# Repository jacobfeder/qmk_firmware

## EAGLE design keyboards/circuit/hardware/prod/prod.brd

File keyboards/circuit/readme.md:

cd to qmk_firmware directory.

Install dependencies using script in util/install_dependencies.sh

```shell
$ sudo util/<your os>_install.sh
```

To program, start keyboard in bootloader mode using BOOTMAGIC by holding down SPACE+B during boot (2-3 sec) then run the following command from the qmk_firmware top level directory (use an on-screen keyboard to press enter key for you to run this command):

```shell
$ make circuit:default:dfu
```

Make your own custom layout by duplicating the "default" folder in keyboards/circuit and modifying as necessary. Flash it to your keyboard by running:

```shell
$ make circuit:<your layout name>:dfu
```

Troubleshooting:

By default Make uses `sh` instead of `bash` for its shell commands. If you are running into strange errors, try using bash instead by calling Make like so:

```shell
$ make circuit:default SHELL=/bin/bash
```

Also, if you get an error that says "bootloader not found" or "device not found", try running the above Make command with ``sudo``.

To program using ICSP run `avrdude_prog_icsp.sh ../../circuit_default_production.hex` in 'keyboards/circuit' directory with arduino as ICSP.

Raw data (keyboard-layout-editor.com):

[{c:"#f67f00",t:"#1a1a1a",a:7},"esc",{c:"#d0ccc0",t:"#000000",a:5},"!\n1","@\n2","#\n3","$\n4","%\n5","^\n6","&\n7","*\n8","(\n9",{a:4,fa:[0,0,0,1]},")\n0\n\n/F10",{c:"#96938e"},"_\n-\n\n/F11","+\n=\n\n/F12",{a:5},"|\n\\","~\n`"],
[{c:"#60605b",t:"#d0ccc0",a:7,w:1.5},"tab",{c:"#d0ccc0",t:"#000000"},"Q","W","E","R","T","Y","U","I","O","P",{c:"#96938e",a:5},"{\n[","}\n]",{c:"#5eb1e7",t:"#1a1a1a",a:4,w:1.5},"\n\n\n/delete\n\n\n\n\n\n<i class='kb kb-Unicode-BackSpace-DeleteLeft-Big'></i>"],
[{c:"#60605b",t:"#d0ccc0",w:1.75},"\n\n\n/caps\n\n\n\n\n\nterminal",{c:"#d0ccc0",t:"#000000",a:7},"A","S","D",{n:true},"F","G","H",{n:true},"J","K","L",{c:"#96938e",a:5},":\n;","\"\n'",{c:"#60605b",t:"#d0ccc0",a:7,w:2.25},"sudo rm -rf /"],
[{w:2.25},"shift",{c:"#d0ccc0",t:"#000000"},"Z","X","C","V","B","N","M",{c:"#96938e",a:5},"<\n,",">\n.","?\n/",{c:"#60605b",t:"#d0ccc0",a:7,w:2.75},"shift"],
[{w:1.5},"ctrl","<i class='fa fa-television'></i>",{w:1.5},"alt",{c:"#d0ccc0",t:"#000000",w:6},"",{c:"#60605b",t:"#d0ccc0"},"fn",{c:"#f67f00",t:"#000000",a:4},"\n\n\n/home\n\n\n\n\n\n<i class='fa fa-chevron-left'></i>","\n\n\n/pgup\n\n\n\n\n\n<i class='fa fa-chevron-up'></i>","\n\n\n/pgdn\n\n\n\n\n\n<i class='fa fa-chevron-down'></i>","\n\n\n/end\n\n\n\n\n\n<i class='fa fa-chevron-right'></i>"]

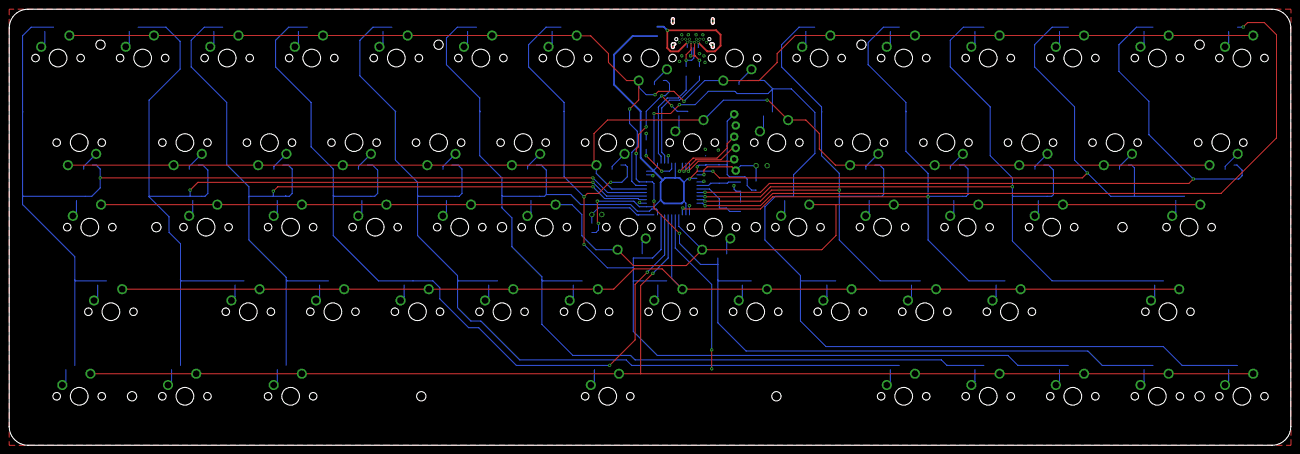
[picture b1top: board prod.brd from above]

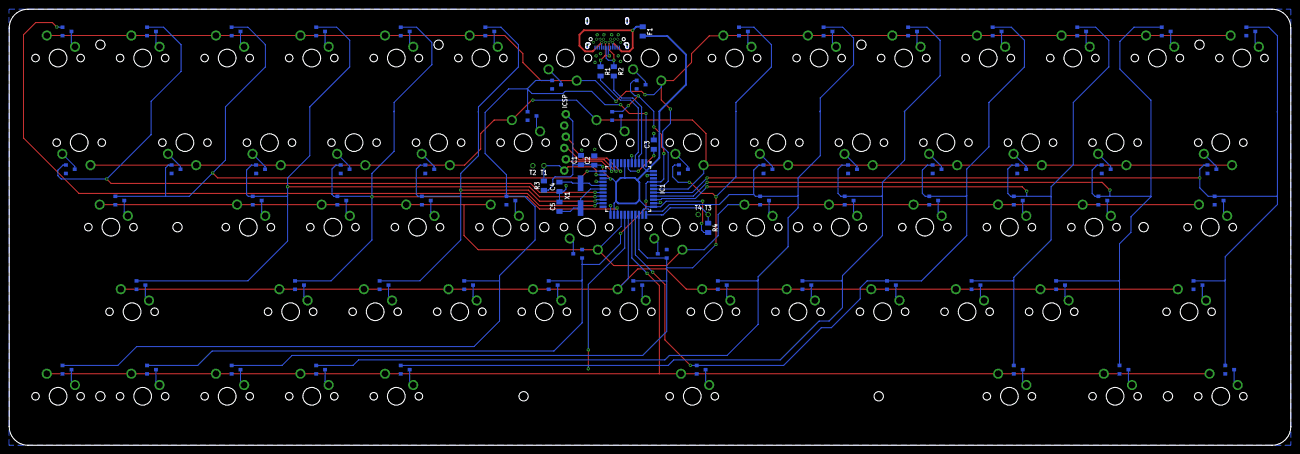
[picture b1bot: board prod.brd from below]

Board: 2 copper layers, 288.7 x 98.2 mm, 144 parts (81 on the bottom side), 98 nets.

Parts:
C1, C3: 1u; 0805
C2: 100n; 0805
C4, C5: 18p; 0805
D_0, D_1, D_2, D_3, D_4, D_5, D_6, D_7, D_8, D_9: DIODE-BAS16L; SOT23-3
D_A: DIODE-BAS16L; SOT23-3
D_B: DIODE-BAS16L; SOT23-3
D_BCK: DIODE-BAS16L; SOT23-3
D_C: DIODE-BAS16L; SOT23-3
D_CAPS: DIODE-BAS16L; SOT23-3
D_COLON: DIODE-BAS16L; SOT23-3
D_D: DIODE-BAS16L; SOT23-3
D_DA: DIODE-BAS16L; SOT23-3
D_E: DIODE-BAS16L; SOT23-3
D_ENTER: DIODE-BAS16L; SOT23-3
D_ESC: DIODE-BAS16L; SOT23-3
D_F: DIODE-BAS16L; SOT23-3
D_FN: DIODE-BAS16L; SOT23-3
D_G: DIODE-BAS16L; SOT23-3
D_GT: DIODE-BAS16L; SOT23-3
D_H: DIODE-BAS16L; SOT23-3
D_I: DIODE-BAS16L; SOT23-3
D_J: DIODE-BAS16L; SOT23-3
D_K: DIODE-BAS16L; SOT23-3
D_L: DIODE-BAS16L; SOT23-3
D_LA: DIODE-BAS16L; SOT23-3
D_LALT: DIODE-BAS16L; SOT23-3
D_LCTRL: DIODE-BAS16L; SOT23-3
D_LCURL: DIODE-BAS16L; SOT23-3
D_LSHIFT: DIODE-BAS16L; SOT23-3
D_LT: DIODE-BAS16L; SOT23-3
D_M: DIODE-BAS16L; SOT23-3
D_MINUS: DIODE-BAS16L; SOT23-3
D_N: DIODE-BAS16L; SOT23-3
D_O: DIODE-BAS16L; SOT23-3
D_OS: DIODE-BAS16L; SOT23-3
D_P: DIODE-BAS16L; SOT23-3
D_PIPE: DIODE-BAS16L; SOT23-3
D_PLUS: DIODE-BAS16L; SOT23-3
D_Q: DIODE-BAS16L; SOT23-3
D_QM: DIODE-BAS16L; SOT23-3
D_QUOTE: DIODE-BAS16L; SOT23-3
D_R: DIODE-BAS16L; SOT23-3
D_RA: DIODE-BAS16L; SOT23-3
D_RCURL: DIODE-BAS16L; SOT23-3
D_RSHIFT: DIODE-BAS16L; SOT23-3
D_S: DIODE-BAS16L; SOT23-3
D_SPACE: DIODE-BAS16L; SOT23-3
D_T: DIODE-BAS16L; SOT23-3
D_TAB: DIODE-BAS16L; SOT23-3
D_TILDE: DIODE-BAS16L; SOT23-3
D_U: DIODE-BAS16L; SOT23-3
D_UA: DIODE-BAS16L; SOT23-3
D_V: DIODE-BAS16L; SOT23-3
D_W: DIODE-BAS16L; SOT23-3
D_X: DIODE-BAS16L; SOT23-3
D_Y: DIODE-BAS16L; SOT23-3
D_Z: DIODE-BAS16L; SOT23-3
F1: 500m; 0805
IC1: ATMEGA32U4; QFP80P1200X1225X120-44
ICSP: HEADER-061X6; HEADER-06
J1: USB-C-2.0-CUI-UJ31-CH-G1-SMT-TR; USB-C-CUI-UJ31-CH-G1-SMT-TR
R1, R2: 22; 0805
R3, R4: 10k; 0805
SW_0, SW_1, SW_2, SW_3, SW_4, SW_5, SW_6, SW_7, SW_8, SW_9: SWITCH-SPSTCHERRY; CHERRY-MX
SW_A: SWITCH-SPSTCHERRY; CHERRY-MX
SW_B: SWITCH-SPSTCHERRY; CHERRY-MX
SW_BCK: SWITCH-SPSTCHERRY; CHERRY-MX
SW_C: SWITCH-SPSTCHERRY; CHERRY-MX
SW_CAPS: SWITCH-SPSTCHERRY; CHERRY-MX
SW_COLON: SWITCH-SPSTCHERRY; CHERRY-MX
SW_D: SWITCH-SPSTCHERRY; CHERRY-MX
SW_DA: SWITCH-SPSTCHERRY; CHERRY-MX
SW_E: SWITCH-SPSTCHERRY; CHERRY-MX
SW_ENTER: SWITCH-SPSTCHERRY; CHERRY-MX
SW_ESC: SWITCH-SPSTCHERRY; CHERRY-MX
SW_F: SWITCH-SPSTCHERRY; CHERRY-MX
SW_FN: SWITCH-SPSTCHERRY; CHERRY-MX
SW_G: SWITCH-SPSTCHERRY; CHERRY-MX
SW_GT: SWITCH-SPSTCHERRY; CHERRY-MX
SW_H: SWITCH-SPSTCHERRY; CHERRY-MX
SW_I: SWITCH-SPSTCHERRY; CHERRY-MX
SW_J: SWITCH-SPSTCHERRY; CHERRY-MX
SW_K: SWITCH-SPSTCHERRY; CHERRY-MX
SW_LA: SWITCH-SPSTCHERRY; CHERRY-MX
SW_LALT: SWITCH-SPSTCHERRY; CHERRY-MX
SW_LCTRL: SWITCH-SPSTCHERRY; CHERRY-MX
SW_LCURL: SWITCH-SPSTCHERRY; CHERRY-MX
SW_LSHIFT: SWITCH-SPSTCHERRY; CHERRY-MX
SW_LT: SWITCH-SPSTCHERRY; CHERRY-MX
SW_M: SWITCH-SPSTCHERRY; CHERRY-MX
SW_MINUS: SWITCH-SPSTCHERRY; CHERRY-MX
SW_N: SWITCH-SPSTCHERRY; CHERRY-MX
SW_O: SWITCH-SPSTCHERRY; CHERRY-MX
SW_OS: SWITCH-SPSTCHERRY; CHERRY-MX
SW_P: SWITCH-SPSTCHERRY; CHERRY-MX
SW_PIPE: SWITCH-SPSTCHERRY; CHERRY-MX
SW_PLUS: SWITCH-SPSTCHERRY; CHERRY-MX
SW_Q: SWITCH-SPSTCHERRY; CHERRY-MX
SW_QM: SWITCH-SPSTCHERRY; CHERRY-MX
SW_QUOTE: SWITCH-SPSTCHERRY; CHERRY-MX
SW_R: SWITCH-SPSTCHERRY; CHERRY-MX
SW_RA: SWITCH-SPSTCHERRY; CHERRY-MX
SW_RCURL: SWITCH-SPSTCHERRY; CHERRY-MX
SW_RSHIFT: SWITCH-SPSTCHERRY; CHERRY-MX
SW_S: SWITCH-SPSTCHERRY; CHERRY-MX
SW_SPACE: SWITCH-SPSTCHERRY; CHERRY-MX
SW_T: SWITCH-SPSTCHERRY; CHERRY-MX
SW_TAB: SWITCH-SPSTCHERRY; CHERRY-MX
SW_TILDE: SWITCH-SPSTCHERRY; CHERRY-MX
SW_U: SWITCH-SPSTCHERRY; CHERRY-MX
SW_UA: SWITCH-SPSTCHERRY; CHERRY-MX
SW_V: SWITCH-SPSTCHERRY; CHERRY-MX
SW_W: SWITCH-SPSTCHERRY; CHERRY-MX
SW_X: SWITCH-SPSTCHERRY; CHERRY-MX
SW_Y: SWITCH-SPSTCHERRY; CHERRY-MX
SW_Z: SWITCH-SPSTCHERRY; CHERRY-MX
S_L: SWITCH-SPSTCHERRY; CHERRY-MX
T1, T2, T3, T4: TEST-POINT
X1: 16MHz; CRYSTAL-SMD

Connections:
COL1: D_CAPS.1, D_ESC.1, D_LCTRL.1, D_LSHIFT.1, D_TAB.1, IC1.38
COL2: D_1.1, D_A.1, D_OS.1, D_Q.1, D_Z.1, IC1.37
COL3: D_2.1, D_LALT.1, D_S.1, D_W.1, D_X.1, IC1.36
COL4: D_3.1, D_C.1, D_D.1, D_E.1, D_SPACE.1, IC1.30
COL5: D_4.1, D_F.1, D_FN.1, D_R.1, D_V.1, IC1.27
COL6: D_5.1, D_B.1, D_G.1, D_LA.1, D_T.1, IC1.32
COL7: D_6.1, D_H.1, D_N.1, D_UA.1, D_Y.1, IC1.31
COL8: D_7.1, D_DA.1, D_J.1, D_M.1, D_U.1, IC1.41
COL9: D_8.1, D_I.1, D_K.1, D_LT.1, D_RA.1, IC1.1
COL10: D_9.1, D_GT.1, D_L.1, D_O.1, IC1.20
COL11: D_0.1, D_COLON.1, D_P.1, D_QM.1, IC1.25
COL12: D_LCURL.1, D_MINUS.1, D_QUOTE.1, D_RSHIFT.1, IC1.19
COL13: D_ENTER.1, D_PLUS.1, D_RCURL.1, IC1.12
COL14: D_BCK.1, D_PIPE.1, IC1.18
COL15: D_TILDE.1, IC1.21
GND: C1.2, C2.2, C3.2, C4.2, C5.1, IC1.5, IC1.15, IC1.23, IC1.35, IC1.43, ICSP.2, J1.GND@1, J1.GND@2, J1.GND@3, J1.GND@4, J1.GND@5, J1.GND@6, J1.GND@7, J1.GND@8, T2.P$1, T4.P$1
unnamed: J1.D+@1, J1.D+@2, R1.1
unnamed: J1.D-@1, J1.D-@2, R2.1
unnamed: IC1.4, R1.2
unnamed: C4.1, IC1.16, X1.P$2
unnamed: F1.1, J1.VBUS@1, J1.VBUS@2, J1.VBUS@3, J1.VBUS@4
unnamed: IC1.3, R2.2
unnamed: IC1.11, ICSP.5
unnamed: C3.1, IC1.6
unnamed: C5.2, IC1.17, X1.P$1
unnamed: D_ESC.3, SW_ESC.P$1
unnamed: IC1.10, ICSP.4
unnamed: IC1.9, ICSP.3
unnamed: IC1.33, R4.2, T3.P$1
unnamed: D_TAB.3, SW_TAB.P$1
unnamed: D_CAPS.3, SW_CAPS.P$1
unnamed: D_LSHIFT.3, SW_LSHIFT.P$1
unnamed: D_LCTRL.3, SW_LCTRL.P$1
unnamed: D_1.3, SW_1.P$1
unnamed: D_Q.3, SW_Q.P$1
unnamed: D_A.3, SW_A.P$1
unnamed: D_Z.3, SW_Z.P$1
unnamed: D_OS.3, SW_OS.P$1
unnamed: D_2.3, SW_2.P$1
unnamed: D_W.3, SW_W.P$1
unnamed: D_S.3, SW_S.P$1
unnamed: D_X.3, SW_X.P$1
unnamed: D_LALT.3, SW_LALT.P$1
unnamed: D_3.3, SW_3.P$1
unnamed: D_E.3, SW_E.P$1
unnamed: D_D.3, SW_D.P$1
unnamed: D_C.3, SW_C.P$1
unnamed: D_SPACE.3, SW_SPACE.P$1
unnamed: D_4.3, SW_4.P$1
unnamed: D_R.3, SW_R.P$1
unnamed: D_F.3, SW_F.P$1
unnamed: D_V.3, SW_V.P$1
unnamed: D_FN.3, SW_FN.P$1
unnamed: D_5.3, SW_5.P$1
unnamed: D_T.3, SW_T.P$1
unnamed: D_G.3, SW_G.P$1
unnamed: D_B.3, SW_B.P$1
unnamed: D_LA.3, SW_LA.P$1
unnamed: D_6.3, SW_6.P$1
unnamed: D_Y.3, SW_Y.P$1
unnamed: D_H.3, SW_H.P$1
unnamed: D_N.3, SW_N.P$1
unnamed: D_UA.3, SW_UA.P$1
unnamed: D_7.3, SW_7.P$1
unnamed: D_U.3, SW_U.P$1
unnamed: D_J.3, SW_J.P$1
unnamed: D_M.3, SW_M.P$1
unnamed: D_DA.3, SW_DA.P$1
unnamed: D_8.3, SW_8.P$1
unnamed: D_I.3, SW_I.P$1
unnamed: D_K.3, SW_K.P$1
unnamed: D_LT.3, SW_LT.P$1
unnamed: D_RA.3, SW_RA.P$1
unnamed: D_9.3, SW_9.P$1
unnamed: D_O.3, SW_O.P$1
unnamed: D_L.3, S_L.P$1
unnamed: D_GT.3, SW_GT.P$1
unnamed: D_0.3, SW_0.P$1
unnamed: D_P.3, SW_P.P$1
unnamed: D_COLON.3, SW_COLON.P$1
unnamed: D_QM.3, SW_QM.P$1
unnamed: D_MINUS.3, SW_MINUS.P$1
unnamed: D_LCURL.3, SW_LCURL.P$1
unnamed: D_QUOTE.3, SW_QUOTE.P$1
unnamed: D_RSHIFT.3, SW_RSHIFT.P$1
unnamed: D_PLUS.3, SW_PLUS.P$1
unnamed: D_RCURL.3, SW_RCURL.P$1
unnamed: D_ENTER.3, SW_ENTER.P$1
unnamed: D_PIPE.3, SW_PIPE.P$1
unnamed: D_BCK.3, SW_BCK.P$1
unnamed: D_TILDE.3, SW_TILDE.P$1
RESET: IC1.13, ICSP.6, R3.1, T1.P$1
ROW1: IC1.40, SW_0.P$2, SW_1.P$2, SW_2.P$2, SW_3.P$2, SW_4.P$2, SW_5.P$2, SW_6.P$2, SW_7.P$2, SW_8.P$2, SW_9.P$2, SW_ESC.P$2, SW_MINUS.P$2, SW_PIPE.P$2, SW_PLUS.P$2, SW_TILDE.P$2
ROW2: IC1.39, SW_BCK.P$2, SW_E.P$2, SW_I.P$2, SW_LCURL.P$2, SW_O.P$2, SW_P.P$2, SW_Q.P$2, SW_R.P$2, SW_RCURL.P$2, SW_T.P$2, SW_TAB.P$2, SW_U.P$2, SW_W.P$2, SW_Y.P$2
ROW3: IC1.26, SW_A.P$2, SW_CAPS.P$2, SW_COLON.P$2, SW_D.P$2, SW_ENTER.P$2, SW_F.P$2, SW_G.P$2, SW_H.P$2, SW_J.P$2, SW_K.P$2, SW_QUOTE.P$2, SW_S.P$2, S_L.P$2
ROW4: IC1.28, SW_B.P$2, SW_C.P$2, SW_GT.P$2, SW_LSHIFT.P$2, SW_LT.P$2, SW_M.P$2, SW_N.P$2, SW_QM.P$2, SW_RSHIFT.P$2, SW_V.P$2, SW_X.P$2, SW_Z.P$2
ROW5: IC1.29, SW_DA.P$2, SW_FN.P$2, SW_LA.P$2, SW_LALT.P$2, SW_LCTRL.P$2, SW_OS.P$2, SW_RA.P$2, SW_SPACE.P$2, SW_UA.P$2
V+5: C1.1, C2.1, F1.2, IC1.2, IC1.7, IC1.14, IC1.24, IC1.34, IC1.44, ICSP.1, R3.2, R4.1

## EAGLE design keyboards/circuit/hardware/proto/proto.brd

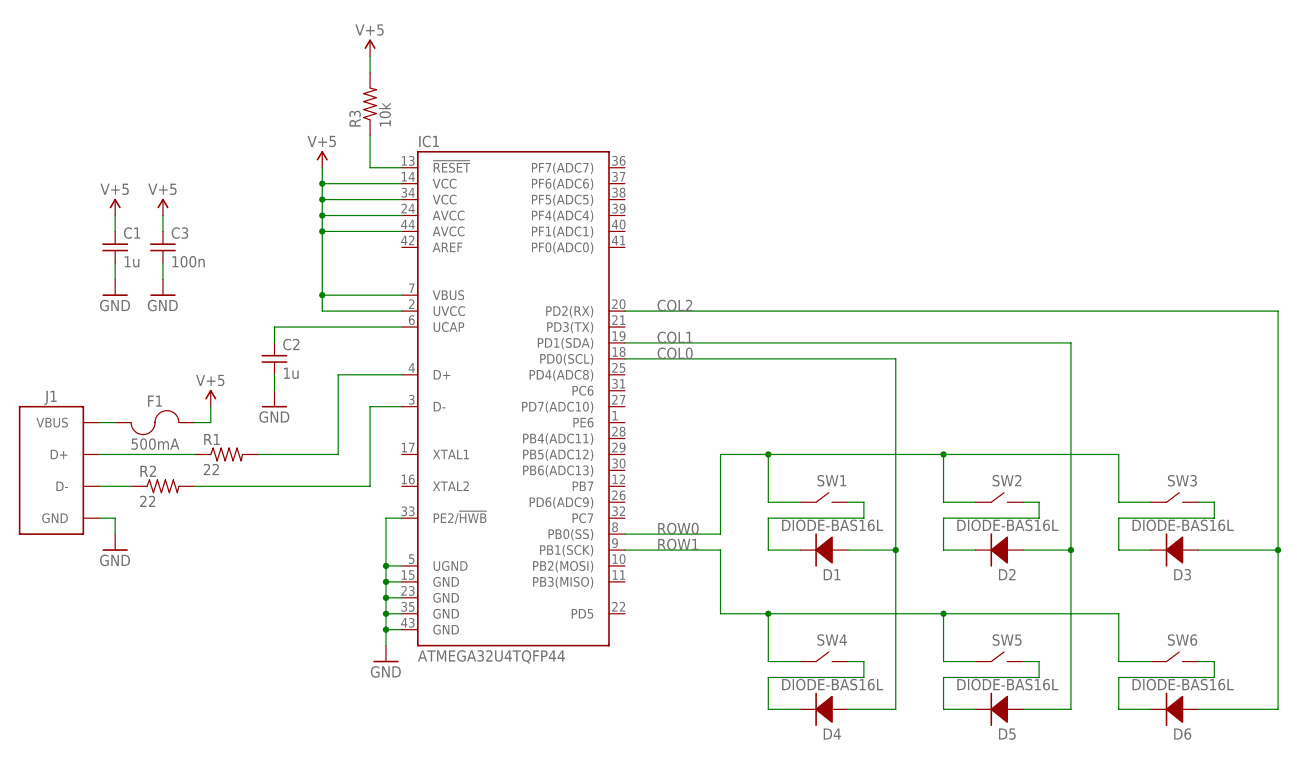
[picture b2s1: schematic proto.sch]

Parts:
C1, C2: 1u; 0805
C3: 100n; 0805
D1, D2, D3, D4, D5, D6: DIODE-BAS16L; SOT23-3
F1: 500mA; 0805
IC1: ATMEGA32U4TQFP44; QFP80P1200X1225X120-44
J1: USB2.0-C; USB-C
R1, R2: 22; 0805
R3: 10k; 0805
SW1, SW2, SW3, SW4, SW5, SW6: SWITCH-SPSTCHERRY; CHERRY-MX

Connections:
COL0: D1.1 (ANODE+), D4.1 (ANODE+), IC1.18 (PD0(SCL))
COL1: D2.1 (ANODE+), D5.1 (ANODE+), IC1.19 (PD1(SDA))
COL2: D3.1 (ANODE+), D6.1 (ANODE+), IC1.20 (PD2(RX))
GND: C1.2, C2.2, C3.2, IC1.5 (UGND), IC1.15 (GND), IC1.23 (GND), IC1.33 (PE2/!HWB), IC1.35 (GND), IC1.43 (GND), J1.GND@1 (GND), J1.GND@2 (GND), J1.GND@3 (GND), J1.GND@4 (GND), J1.GND@5 (GND), J1.GND@6 (GND), J1.GND@7 (GND), J1.GND@8 (GND), J1.GND@9 (GND), J1.GND@10 (GND), J1.GND@11 (GND), J1.GND@12 (GND), J1.GND@13 (GND), J1.GND@14 (GND), J1.GND@15 (GND), J1.GND@16 (GND)
unnamed: J1.D+@1 (D+), J1.D+@2 (D+), R1.1
unnamed: J1.D-@1 (D-), J1.D-@2 (D-), R2.1
unnamed: F1.1, J1.VBUS@1 (VBUS), J1.VBUS@2 (VBUS), J1.VBUS@3 (VBUS), J1.VBUS@4 (VBUS)
unnamed: C2.1, IC1.6 (UCAP)
unnamed: IC1.4 (D+), R1.2
unnamed: IC1.3 (D-), R2.2
unnamed: IC1.13 (!RESET), R3.1
unnamed: D1.3 (CATHODE-), SW1.P$2
unnamed: D2.3 (CATHODE-), SW2.P$2
unnamed: D3.3 (CATHODE-), SW3.P$2
unnamed: D4.3 (CATHODE-), SW4.P$2
unnamed: D5.3 (CATHODE-), SW5.P$2
unnamed: D6.3 (CATHODE-), SW6.P$2
ROW0: IC1.8 (PB0(SS)), SW1.P$1, SW2.P$1, SW3.P$1
ROW1: IC1.9 (PB1(SCK)), SW4.P$1, SW5.P$1, SW6.P$1
V+5: C1.1, C3.1, F1.2, IC1.2 (UVCC), IC1.7 (VBUS), IC1.14 (VCC), IC1.24 (AVCC), IC1.34 (VCC), IC1.44 (AVCC), R3.2

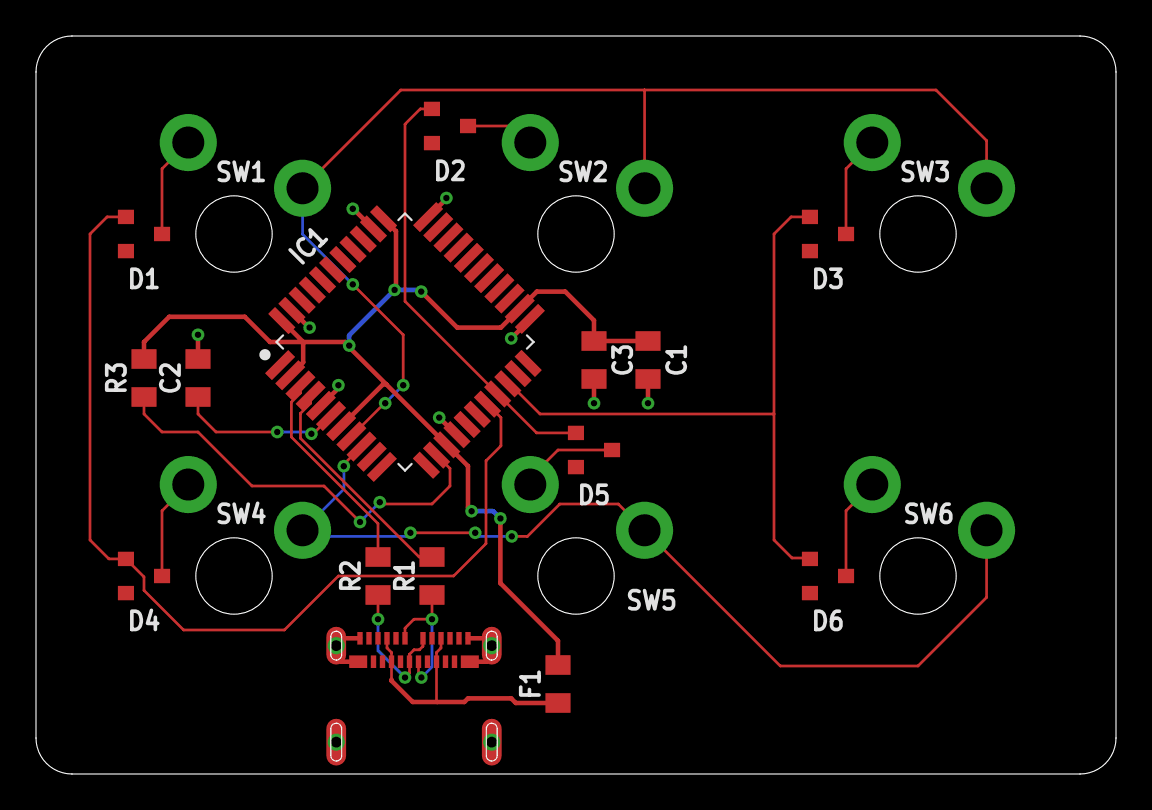
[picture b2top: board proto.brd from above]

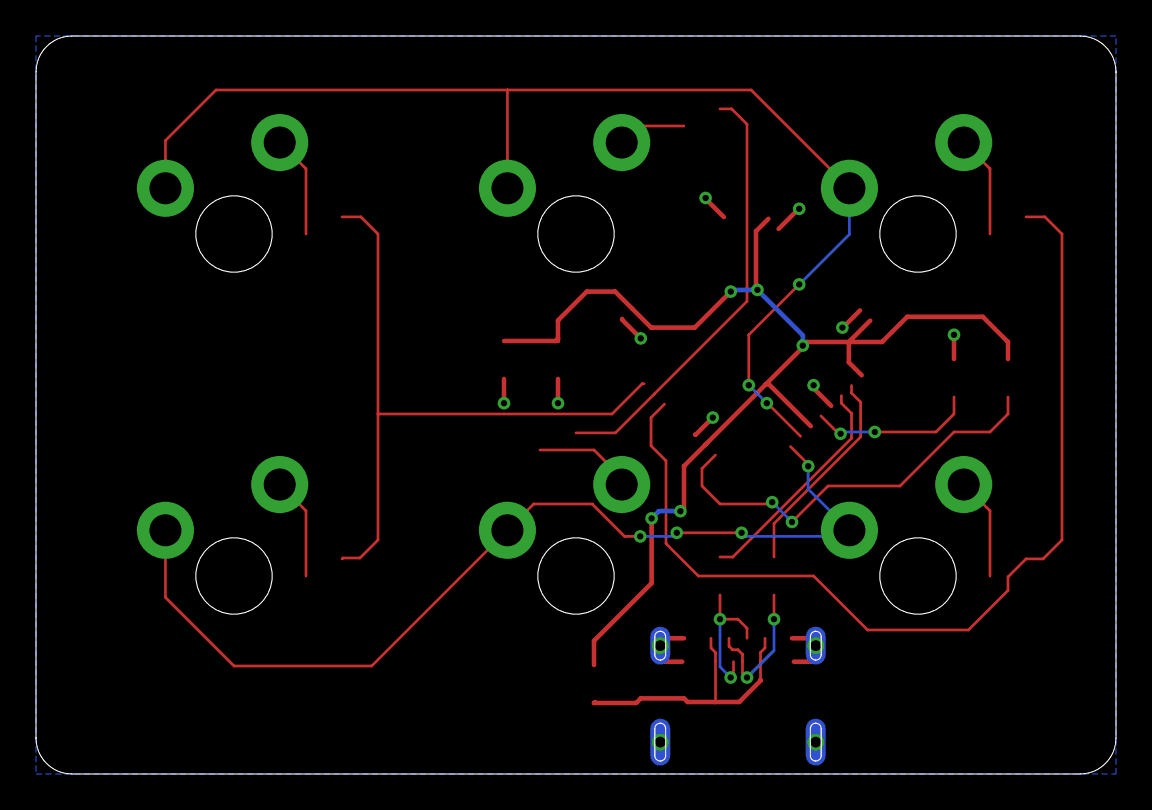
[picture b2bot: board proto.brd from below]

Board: 2 copper layers, 60.0 x 41.0 mm, 21 parts (6 on the bottom side), 20 nets.

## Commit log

2018-04-08 added ben mediakeyboard
2018-04-08 updated circuit kbd and changed salt+bootloader keys for bootmagic
2018-04-26 production hw
2018-04-26 added circuit keyboard layout; bootloader is failing build
2018-04-29 updated keymap to use space cadet; fixed bootloader not building problem
2018-05-02 updated pinout to match pcb
2018-05-04 fix keymapping
2018-05-08 added home/end and fixed tapping toggle on fn key
2018-05-09 added ctrl+alt+del and alt+f4 shortcuts to FN layer
2018-05-10 added lock command to shortcut -> fn+L
2018-05-29 added transparent keys, added calc shortcut, removed tap toggle for FN key
2018-06-07 initial
2018-06-07 highlight boot command in readme
2018-07-25 add dependency installs to readme
2018-07-26 jacob vol buttons
2018-11-12 remove space cadet, switch to normal shifting
2019-01-14 fix reversed PGUP and PGDN keys
2019-07-23 replace KC_ESC with KC_GESC: shift + esc = tilde
